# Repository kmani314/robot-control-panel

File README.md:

# robot control panel

## Description
The main goal of this project is to create a framework for building mechanism-specific control devices. An example is a robotic arm controller that is a scaled down version of the arm itself. Similarities between the controller and the mechanism can make for a more effective controller and can also flatten the learning curve.

### Mainboard
The mainboard is a generic STM32 based breakout with USB Type-C. It has 6 analog and 12 digital inputs, in addition to two I<sup>2</sup>C ports. This board can be used to build any kind of controller because it does not have any specific hardware.

### Testing software
The testing software is a basic webapp that simulates a 'robot' with basic drag and friction. The idea was to create something that is not entirely unlike driving an actual robot. Then, a number of points are scattered on the screen in a random pattern. The goal is to pass through all of them in a certain order as fast as possible, like the actual robot driving test.

[Video](https://www.youtube.com/watch?v=zxHl_gj8LcE)

### Controller
I think that the ideal physical controller design centers around the idea of one person controlling the whole robot. I think that having multiple drivers splits a task that is doable by one person over two people who cannot communicate perfectly. If one person could control both the drive system and the manipulators at the same time with good dexterity, it would be possible to coordinate motions much more efficiently. The problem is that Xbox controllers are not ideal, so trying to fit all of these controls on one controller is not worth it.

Additionally, this isn't just a hardware problem. I think that the proper use of abstraction on the robot code side can drastically reduce the amount of input necessary from the driver. It is true that this can take away a sense of full control that the driver likes to have, but I feel like this can be easily solved with practice and optimization. Remember that this optimization is toward the goal of having one person drive the robot alone, which would be very beneficial.

Although software optimization only takes one so far. The controller itself is where the most optimizations can be made. Through some code improvements, it should be possible to drive only with one stick. Then, this other stick can be used specifically for manipulators, which can be selected through some button combination. Or, this second stick could be swapped out with some mechanism specific to some manipulator. This board supports anything with potentiometers.

The controller I designed uses RC transmitter joysticks in place of the smaller joysticks on Xbox controllers. The larger joysticks have better accuracy due to their increased travel but at the expense of time to reach an extreme. The increased travel is possibly more important because these sticks are meant to be used with any number of different manipulators. There are swappable button plates on the back.

There are no mechanism specific control devices in this controller, but they could easily be added with a few new parts. An elevator, for example, could be controlled by a joystick that does not have the Y axis spring, so that its motion mimics the motion of the elevator. Or it could be entirely swapped out. 

### Improvements
I don't think there are many improvements to be made on the mainboard. It's pretty simple and it worked on the first try. The ADC is not too noisy and the digital inputs/I<sup>2</sup>C have no problems.

The testing software is too simplistic. It doesn't test manipulators and has no way to test button-joystick coordination. A second revision would probably have a better (maybe 3D) simulation of a game field complete with better physics and collision detection. There really isn't a better way to test these controllers other than actually trying to simulate the thing they will be used for. This would require almost a complete rewrite.

The controller itself is rudimentary. If this were designed with an actual robot in mind, it would probably look nothing like this. I just wanted something that demonstrated the concepts I was going for. I would start from scratch if I were to redo this controller for some robot.

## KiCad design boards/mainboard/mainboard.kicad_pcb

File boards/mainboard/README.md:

# Mainboard

This is the main board for the control panel. It is a [STM32F042K6T6](https://lcsc.com/product-detail/ST-Microelectronics_STMicroelectronics_STM32F042K6T6_STM32F042K6T6_C69216.html) with a [USB Type-C Connector](https://lcsc.com/product-detail/USB-Type-C_TYPE-C-31-M-12-Female-16P-SMD_C165948.html) and 12 analog/digital I/O pins broken out with JST-XH connectors. It also has two I2C connectors and a separate power connector that goes straight to the regulator that supports up to 15v input.

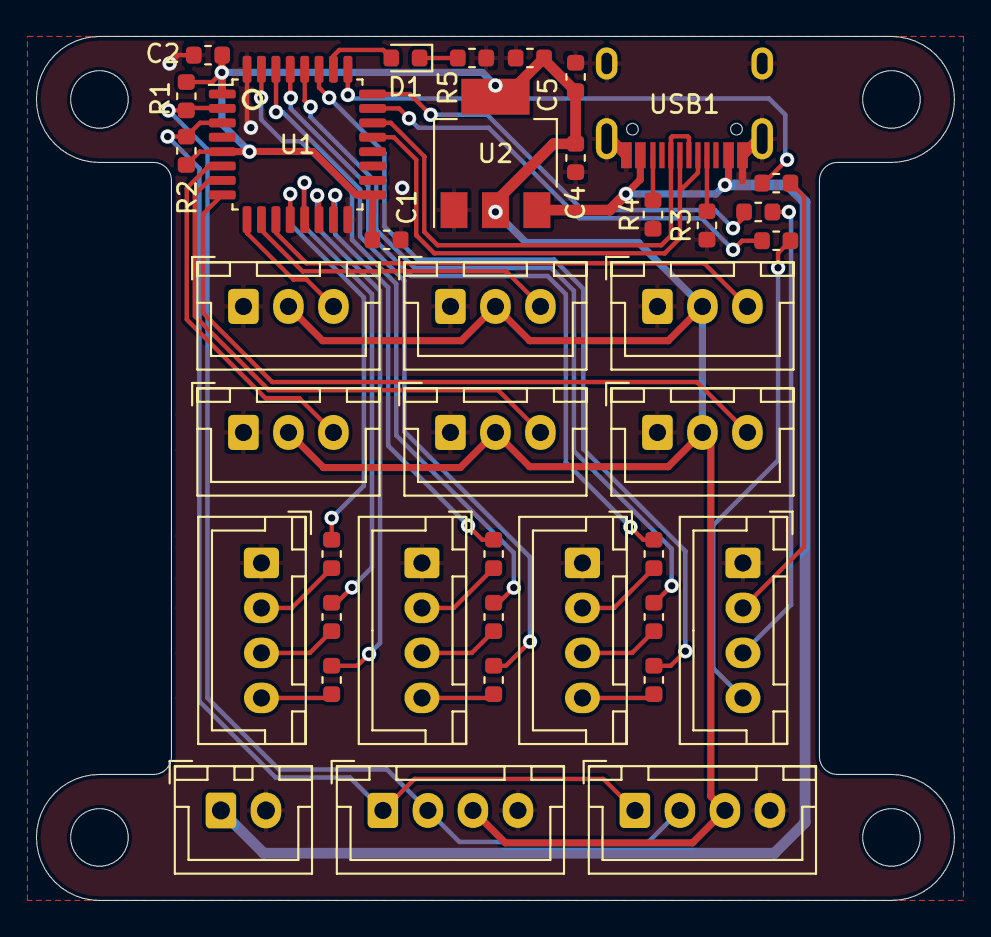
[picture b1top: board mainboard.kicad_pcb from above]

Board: 2 copper layers, 51.0 x 48.0 mm, 43 parts (0 on the bottom side), 41 nets.

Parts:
C1, C2, C3: 0.1uF; C_0603_1608Metric
C4, C5: 4.7uF; C_0603_1608Metric
D1: LED; LED_0603_1608Metric
H1, H2, H3, H4: MountingHole; MountingHole_3.2mm_M3
J1, J2, J8, J9, J10, J12: Conn_01x04_Female; JST_XH_B4B-XH-A_1x04_P2.50mm_Vertical
J3, J4, J5, J6, J7, J11: Conn_01x03_Female; JST_XH_B3B-XH-A_1x03_P2.50mm_Vertical
J15: Conn_01x02_Female; JST_XH_B2B-XH-A_1x02_P2.50mm_Vertical
R1, R2: 4.7k; R_0603_1608Metric
R3, R4: 5.1k; R_0603_1608Metric
R5: 15; R_0603_1608Metric
R6, R7, R8, R9, R10, R11, R12, R13, R14, R15, R16, R17: 1k; R_0603_1608Metric
U1: STM32F042K6Tx; LQFP-32_7x7mm_P0.8mm
U2: LD1117S33TR_SOT223; SOT-223-3_TabPin2
USB1: 12401598E4#2A; HRO-TYPE-C-31-M-12

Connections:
+3V3: C1.1, C2.1, C3.1, C4.1, C5.1, J1.3, J2.3, J3.2, J4.2, J5.2, J6.2, J7.2, J11.2, R1.2, R2.1, U1.1, U1.5, U1.17, U2.2
/A0: J3.3, U1.11
/A1: J4.3, U1.10
/A2: J5.3, U1.9
/A3: J6.3, U1.6
/A4: J7.3, U1.7
/A5: J11.3, U1.8
/D0: R6.1, U1.12
/D1: R7.1, U1.13
/D2: R8.1, U1.14
/D3: R9.1, U1.15
/D4: R10.1, U1.31
/D5: R11.1, U1.30
/D6: R12.1, U1.29
/D7: R13.1, U1.28
/D8: R14.1, U1.27
/D9: R15.1, U1.25
/D10: R16.1, U1.24
/D11: R17.1, U1.23
/D+: U1.22, USB1.A6, USB1.B6
/D-: U1.21, USB1.A7, USB1.B7
/SCL: J1.2, J2.2, R1.1, U1.2
/SDA: J1.1, J2.1, R2.2, U1.3
GND: C1.2, C2.2, C3.2, C4.2, C5.2, J1.4, J2.4, J3.1, J4.1, J5.1, J6.1, J7.1, J8.1, J9.1, J10.1, J11.1, J12.1, J15.2, R3.1, R4.2, R5.1, U1.16, U1.32, U2.1, USB1.A1, USB1.B1, USB1.S1, USB1.S2, USB1.S3, USB1.S4
unnamed: D1.1, R5.2
unnamed: D1.2, U1.26
unnamed: J8.2, R6.2
unnamed: J8.3, R7.2
unnamed: J8.4, R8.2
unnamed: J9.2, R9.2
unnamed: J9.3, R10.2
unnamed: J9.4, R11.2
unnamed: J10.2, R12.2
unnamed: J10.3, R13.2
unnamed: J10.4, R14.2
unnamed: J12.2, R15.2
unnamed: J12.3, R16.2
unnamed: J12.4, R17.2
unnamed: R3.2, USB1.A5
unnamed: R4.1, USB1.B5
VBUS: J15.1, U2.3, USB1.A4, USB1.B4

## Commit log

2020-07-11 initial commit, readme, license
2020-07-11 fix readme typo
2020-07-14 add mainboard + readme
2020-07-14 try to fix image url
2020-07-14 remove gerber
2020-07-14 gitignore fix
2020-07-17 address issues
2020-07-31 restructure and add tester
2020-07-31 chrome optimizations
2020-07-31 npm build
2020-07-31 Initial dist subtree commit
2020-07-31 dist gitignore
2020-08-01 add image
2020-08-29 add step and other stuff
2020-09-05 final commit
2020-09-05 final commit 2
2020-12-13 Bump ini from 1.3.5 to 1.3.8 in /testing-software
    Bumps [ini](https://github.com/isaacs/ini) from 1.3.5 to 1.3.8.
    - [Release notes](https://github.com/isaacs/ini/releases)
    - [Commits](https://github.com/isaacs/ini/compare/v1.3.5...v1.3.8)
2021-04-01 Bump y18n from 4.0.0 to 4.0.1 in /testing-software
    Bumps [y18n](https://github.com/yargs/y18n) from 4.0.0 to 4.0.1.
    - [Release notes](https://github.com/yargs/y18n/releases)
    - [Changelog](https://github.com/yargs/y18n/blob/master/CHANGELOG.md)
    - [Commits](https://github.com/yargs/y18n/commits)
2021-04-30 Bump ssri from 6.0.1 to 6.0.2 in /testing-software
    Bumps [ssri](https://github.com/npm/ssri) from 6.0.1 to 6.0.2.
    - [Release notes](https://github.com/npm/ssri/releases)
    - [Changelog](https://github.com/npm/ssri/blob/v6.0.2/CHANGELOG.md)
    - [Commits](https://github.com/npm/ssri/compare/v6.0.1...v6.0.2)
2021-05-10 Bump url-parse from 1.4.7 to 1.5.1 in /testing-software
    Bumps [url-parse](https://github.com/unshiftio/url-parse) from 1.4.7 to 1.5.1.
    - [Release notes](https://github.com/unshiftio/url-parse/releases)
    - [Commits](https://github.com/unshiftio/url-parse/compare/1.4.7...1.5.1)
2021-05-11 Bump lodash from 4.17.19 to 4.17.21 in /testing-software
    Bumps [lodash](https://github.com/lodash/lodash) from 4.17.19 to 4.17.21.
    - [Release notes](https://github.com/lodash/lodash/releases)
    - [Commits](https://github.com/lodash/lodash/compare/4.17.19...4.17.21)
2021-05-11 Bump hosted-git-info from 2.8.8 to 2.8.9 in /testing-software
    Bumps [hosted-git-info](https://github.com/npm/hosted-git-info) from 2.8.8 to 2.8.9.
    - [Release notes](https://github.com/npm/hosted-git-info/releases)
    - [Changelog](https://github.com/npm/hosted-git-info/blob/v2.8.9/CHANGELOG.md)
    - [Commits](https://github.com/npm/hosted-git-info/compare/v2.8.8...v2.8.9)
2021-05-26 Bump browserslist from 4.13.0 to 4.16.6 in /testing-software
    Bumps [browserslist](https://github.com/browserslist/browserslist) from 4.13.0 to 4.16.6.
    - [Release notes](https://github.com/browserslist/browserslist/releases)
    - [Changelog](https://github.com/browserslist/browserslist/blob/main/CHANGELOG.md)
    - [Commits](https://github.com/browserslist/browserslist/compare/4.13.0...4.16.6)
2021-05-28 Bump dns-packet from 1.3.1 to 1.3.4 in /testing-software
    Bumps [dns-packet](https://github.com/mafintosh/dns-packet) from 1.3.1 to 1.3.4.
    - [Release notes](https://github.com/mafintosh/dns-packet/releases)
    - [Changelog](https://github.com/mafintosh/dns-packet/blob/master/CHANGELOG.md)
    - [Commits](https://github.com/mafintosh/dns-packet/compare/v1.3.1...v1.3.4)
2021-06-06 Bump ws from 6.2.1 to 6.2.2 in /testing-software
    Bumps [ws](https://github.com/websockets/ws) from 6.2.1 to 6.2.2.
    - [Release notes](https://github.com/websockets/ws/releases)
    - [Commits](https://github.com/websockets/ws/commits)
    ---
    updated-dependencies:
    - dependency-name: ws
2021-06-17 Bump postcss from 7.0.32 to 7.0.36 in /testing-software
    Bumps [postcss](https://github.com/postcss/postcss) from 7.0.32 to 7.0.36.
    - [Release notes](https://github.com/postcss/postcss/releases)
    - [Changelog](https://github.com/postcss/postcss/blob/main/CHANGELOG.md)
    - [Commits](https://github.com/postcss/postcss/compare/7.0.32...7.0.36)
    ---
    updated-dependencies:
2021-08-12 Bump path-parse from 1.0.6 to 1.0.7 in /testing-software
    Bumps [path-parse](https://github.com/jbgutierrez/path-parse) from 1.0.6 to 1.0.7.
    - [Release notes](https://github.com/jbgutierrez/path-parse/releases)
    - [Commits](https://github.com/jbgutierrez/path-parse/commits/v1.0.7)
    ---
    updated-dependencies:
    - dependency-name: path-parse
2021-10-06 Bump url-parse from 1.4.7 to 1.5.3 in /testing-software
    Bumps [url-parse](https://github.com/unshiftio/url-parse) from 1.4.7 to 1.5.3.
    - [Release notes](https://github.com/unshiftio/url-parse/releases)
    - [Commits](https://github.com/unshiftio/url-parse/compare/1.4.7...1.5.3)
    ---
    updated-dependencies:
    - dependency-name: url-parse
2022-01-14 Bump follow-redirects from 1.12.1 to 1.14.7 in /testing-software
    Bumps [follow-redirects](https://github.com/follow-redirects/follow-redirects) from 1.12.1 to 1.14.7.
    - [Release notes](https://github.com/follow-redirects/follow-redirects/releases)
    - [Commits](https://github.com/follow-redirects/follow-redirects/compare/v1.12.1...v1.14.7)
    ---
    updated-dependencies:
    - dependency-name: follow-redirects
2022-02-13 Bump follow-redirects from 1.12.1 to 1.14.8 in /testing-software
    Bumps [follow-redirects](https://github.com/follow-redirects/follow-redirects) from 1.12.1 to 1.14.8.
    - [Release notes](https://github.com/follow-redirects/follow-redirects/releases)
    - [Commits](https://github.com/follow-redirects/follow-redirects/compare/v1.12.1...v1.14.8)
    ---
    updated-dependencies:
    - dependency-name: follow-redirects
2022-02-19 Bump url-parse from 1.4.7 to 1.5.7 in /testing-software
    Bumps [url-parse](https://github.com/unshiftio/url-parse) from 1.4.7 to 1.5.7.
    - [Release notes](https://github.com/unshiftio/url-parse/releases)
    - [Commits](https://github.com/unshiftio/url-parse/compare/1.4.7...1.5.7)
    ---
    updated-dependencies:
    - dependency-name: url-parse
2022-02-27 Bump url-parse from 1.4.7 to 1.5.10 in /testing-software
    Bumps [url-parse](https://github.com/unshiftio/url-parse) from 1.4.7 to 1.5.10.
    - [Release notes](https://github.com/unshiftio/url-parse/releases)
    - [Commits](https://github.com/unshiftio/url-parse/compare/1.4.7...1.5.10)
    ---
    updated-dependencies:
    - dependency-name: url-parse
2022-03-27 Bump minimist from 1.2.5 to 1.2.6 in /testing-software
    Bumps [minimist](https://github.com/substack/minimist) from 1.2.5 to 1.2.6.
    - [Release notes](https://github.com/substack/minimist/releases)
    - [Commits](https://github.com/substack/minimist/compare/1.2.5...1.2.6)
    ---
    updated-dependencies:
    - dependency-name: minimist
2022-04-29 Bump async from 2.6.3 to 2.6.4 in /testing-software
    Bumps [async](https://github.com/caolan/async) from 2.6.3 to 2.6.4.
    - [Release notes](https://github.com/caolan/async/releases)
    - [Changelog](https://github.com/caolan/async/blob/v2.6.4/CHANGELOG.md)
    - [Commits](https://github.com/caolan/async/compare/v2.6.3...v2.6.4)
    ---
    updated-dependencies:
2022-06-01 Bump eventsource from 1.0.7 to 1.1.1 in /testing-software
    Bumps [eventsource](https://github.com/EventSource/eventsource) from 1.0.7 to 1.1.1.
    - [Release notes](https://github.com/EventSource/eventsource/releases)
    - [Changelog](https://github.com/EventSource/eventsource/blob/master/HISTORY.md)
    - [Commits](https://github.com/EventSource/eventsource/compare/v1.0.7...v1.1.1)
    ---
    updated-dependencies:
2022-07-21 Bump terser from 4.8.0 to 4.8.1 in /testing-software
    Bumps [terser](https://github.com/terser/terser) from 4.8.0 to 4.8.1.
    - [Release notes](https://github.com/terser/terser/releases)
    - [Changelog](https://github.com/terser/terser/blob/master/CHANGELOG.md)
    - [Commits](https://github.com/terser/terser/commits)
    ---
    updated-dependencies:
2022-11-13 Bump loader-utils from 1.4.0 to 1.4.2 in /testing-software
    Bumps [loader-utils](https://github.com/webpack/loader-utils) from 1.4.0 to 1.4.2.
    - [Release notes](https://github.com/webpack/loader-utils/releases)
    - [Changelog](https://github.com/webpack/loader-utils/blob/v1.4.2/CHANGELOG.md)
    - [Commits](https://github.com/webpack/loader-utils/compare/v1.4.0...v1.4.2)
    ---
    updated-dependencies:
2022-12-06 Bump decode-uri-component from 0.2.0 to 0.2.2 in /testing-software
    Bumps [decode-uri-component](https://github.com/SamVerschueren/decode-uri-component) from 0.2.0 to 0.2.2.
    - [Release notes](https://github.com/SamVerschueren/decode-uri-component/releases)
    - [Commits](https://github.com/SamVerschueren/decode-uri-component/compare/v0.2.0...v0.2.2)
    ---
    updated-dependencies:
    - dependency-name: decode-uri-component
2022-12-08 Bump qs and express in /testing-software
    Bumps [qs](https://github.com/ljharb/qs) and [express](https://github.com/expressjs/express). These dependencies needed to be updated together.
    Updates `qs` from 6.7.0 to 6.11.0
    - [Release notes](https://github.com/ljharb/qs/releases)
    - [Changelog](https://github.com/ljharb/qs/blob/main/CHANGELOG.md)
    - [Commits](https://github.com/ljharb/qs/compare/v6.7.0...v6.11.0)
    Updates `express` from 4.17.1 to 4.18.2
2022-12-13 Bump express from 4.17.1 to 4.18.2 in /testing-software
    Bumps [express](https://github.com/expressjs/express) from 4.17.1 to 4.18.2.
    - [Release notes](https://github.com/expressjs/express/releases)
    - [Changelog](https://github.com/expressjs/express/blob/master/History.md)
    - [Commits](https://github.com/expressjs/express/compare/4.17.1...4.18.2)
    ---
    updated-dependencies:
2023-01-01 Bump json5, tsconfig-paths, html-webpack-plugin, webpack and webpack-cli
    Bumps [json5](https://github.com/json5/json5) to 2.2.3 and updates ancestor dependencies [json5](https://github.com/json5/json5), [tsconfig-paths](https://github.com/dividab/tsconfig-paths), [html-we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
    Updates `json5` from 2.1.3 to 2.2.3
    - [Release notes](https://github.com/json5/json5/releases)
    - [Changelog](https://github.com/json5/json5/blob/main/CHANGELOG.md)
    - [Commits](https://github.com/json5/json5/co
2023-01-07 Bump json5 from 1.0.1 to 1.0.2 in /testing-software
    Bumps [json5](https://github.com/json5/json5) from 1.0.1 to 1.0.2.
    - [Release notes](https://github.com/json5/json5/releases)
    - [Changelog](https://github.com/json5/json5/blob/main/CHANGELOG.md)
    - [Commits](https://github.com/json5/json5/compare/v1.0.1...v1.0.2)
    ---
    updated-dependencies:

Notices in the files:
README.md:
License: MIT
